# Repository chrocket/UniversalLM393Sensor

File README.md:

# UniversalLM393Sensor
Sensor board input to LM393. Outputs digital and analog;  Knock off of many that are out there

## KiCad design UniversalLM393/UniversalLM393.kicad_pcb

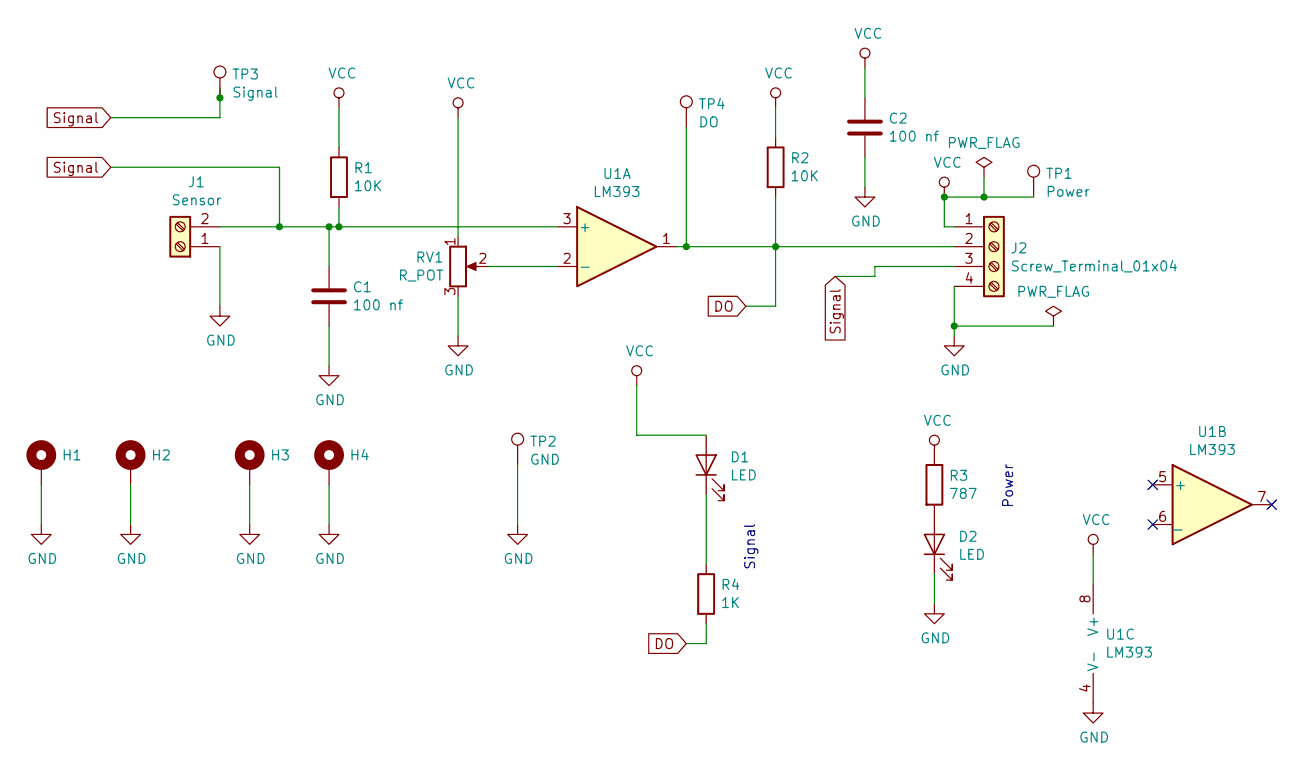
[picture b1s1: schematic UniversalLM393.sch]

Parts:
C1, C2: 100 nf; C_0805_2012Metric
D1, D2: LED; D_0805_2012Metric
H1, H2, H3, H4: MountingHole_2.5mm_Pad_Via
J1: Sensor; TerminalBlock_TE_282834-2_1x02_P2.54mm_Horizontal
J2: Screw_Terminal_01x04; PinHeader_1x04_P2.54mm_Vertical
R1, R2: 10K; R_0805_2012Metric
R3: 787; R_0805_2012Metric
R4: 1K; R_0805_2012Metric
RV1: R_POT; Potentiometer_ACP_CA9-VSMD_Vertical
TP1: Power; TestPoint_Keystone_5000-5004_Miniature
TP2: GND; TestPoint_Keystone_5000-5004_Miniature
TP3: Signal; TestPoint_Keystone_5000-5004_Miniature
TP4: DO; TestPoint_Keystone_5000-5004_Miniature
U1: LM393; SO-8_5.3x6.2mm_P1.27mm

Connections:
DO: J2.2, R2.2, R4.2, TP4.1, U1.1
GND: C1.2, C2.2, D2.1 (K), H1.1, H2.1, H3.1, H4.1, J1.1, J2.4, RV1.3, TP2.1, U1.4 (V-)
unnamed: D1.1 (K), R4.1
unnamed: D2.2 (A), R3.2
unnamed: RV1.2, U1.2 (-)
Signal: C1.1, J1.2, J2.3, R1.2, TP3.1, U1.3 (+)
VCC: C2.1, D1.2 (A), J2.1, R1.1, R2.1, R3.1, RV1.1, TP1.1, U1.8 (V+)

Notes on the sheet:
Power
Signal

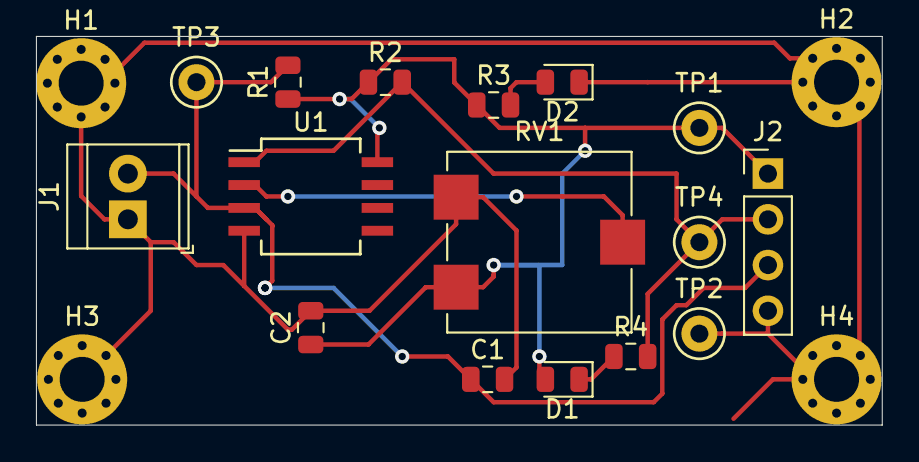
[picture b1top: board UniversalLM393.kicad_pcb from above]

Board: 2 copper layers, 47.0 x 21.6 mm, 20 parts (0 on the bottom side), 7 nets.

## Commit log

2020-01-23 Initial upload
